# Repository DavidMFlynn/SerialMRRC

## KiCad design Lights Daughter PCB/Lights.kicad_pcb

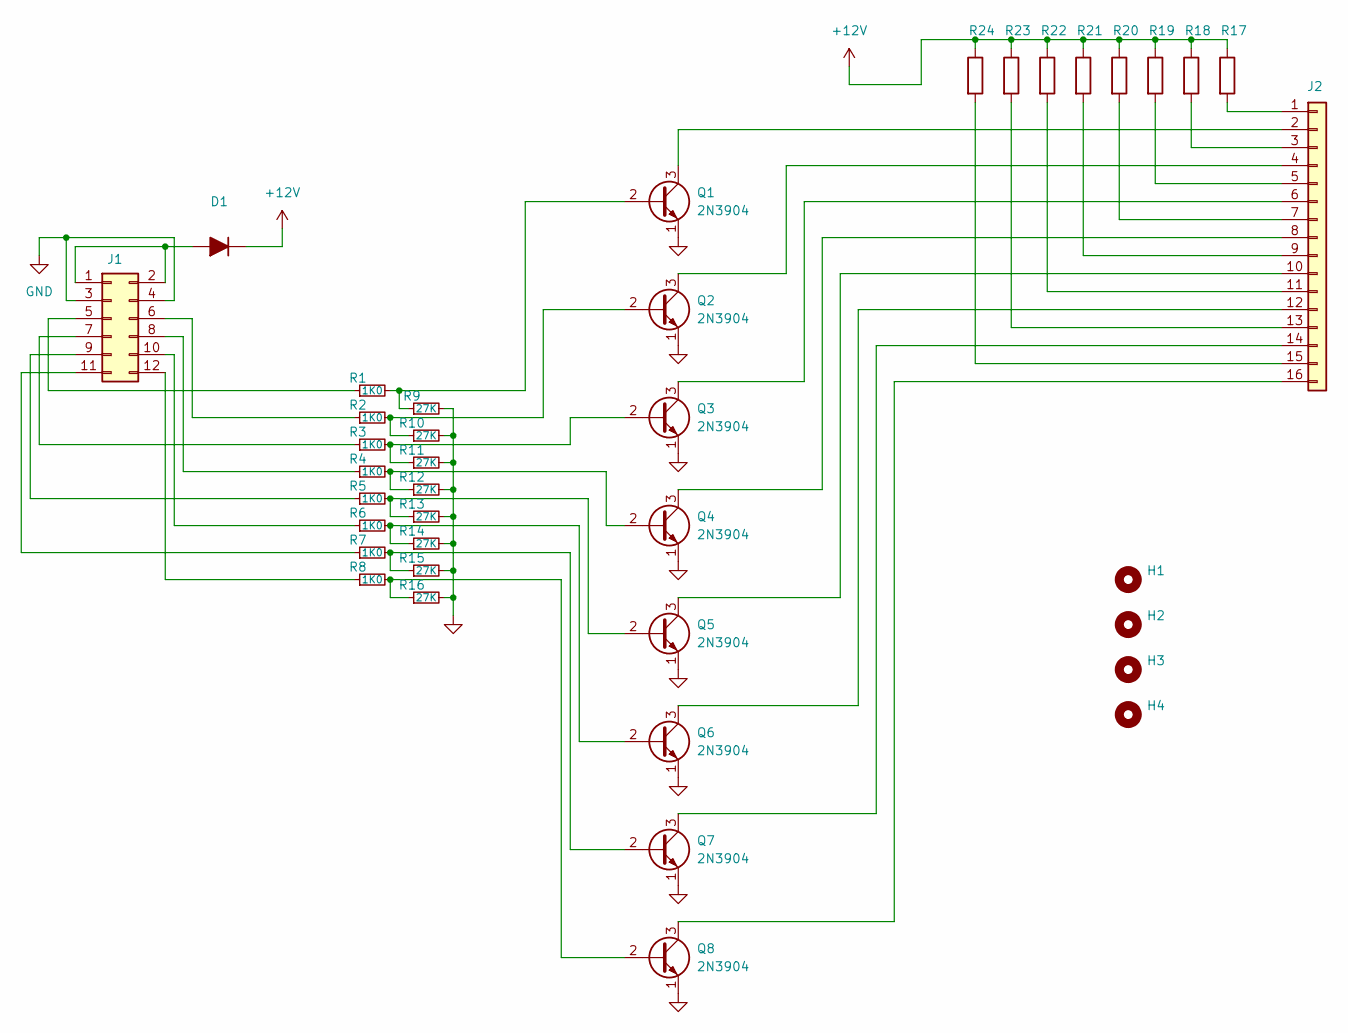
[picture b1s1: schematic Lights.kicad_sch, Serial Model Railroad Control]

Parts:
D1: SMA; D_SMA_Handsoldering
H1, H2, H3, H4: MountingHole; MountingHole_3.2mm_M3
J1: Conn_02x06_Odd_Even; PinHeader_2x06_P2.54mm_Vertical
J2: Conn_01x16; TerminalBlock_Phoenix_PT-1,5-16-3.5-H_1x16_P3.50mm_Horizont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
Q1, Q2, Q3, Q4, Q5, Q6, Q7, Q8: 2N3904; TO-92_Inline
R1, R2, R3, R4, R5, R6, R7, R8: 1K0; R_0805_2012Metric_Pad1.20x1.40mm_HandSolder
R9, R10, R11, R12, R13, R14, R15, R16: 27K; R_0805_2012Metric_Pad1.20x1.40mm_HandSolder
R17, R18, R19, R20, R21, R22, R23, R24: 1K0; R_Axial_DIN0207_L6.3mm_D2.5mm_P10.16mm_Horizontal

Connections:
+12V: D1.1 (K), R17.1, R18.1, R19.1, R20.1, R21.1, R22.1, R23.1, R24.1
GND: J1.3, J1.4, Q1.1 (E), Q2.1 (E), Q3.1 (E), Q4.1 (E), Q5.1 (E), Q6.1 (E), Q7.1 (E), Q8.1 (E), R9.2, R10.2, R11.2, R12.2, R13.2, R14.2, R15.2, R16.2
unnamed: D1.2 (A), J1.1, J1.2
unnamed: J1.5, R1.1
unnamed: J1.6, R2.1
unnamed: J1.7, R3.1
unnamed: J1.8, R4.1
unnamed: J1.9, R5.1
unnamed: J1.10, R6.1
unnamed: J1.11, R7.1
unnamed: J1.12, R8.1
unnamed: J2.1, R17.2
unnamed: J2.2, Q1.3 (C)
unnamed: J2.3, R18.2
unnamed: J2.4, Q2.3 (C)
unnamed: J2.5, R19.2
unnamed: J2.6, Q3.3 (C)
unnamed: J2.7, R20.2
unnamed: J2.8, Q4.3 (C)
unnamed: J2.9, R21.2
unnamed: J2.10, Q5.3 (C)
unnamed: J2.11, R22.2
unnamed: J2.12, Q6.3 (C)
unnamed: J2.13, R23.2
unnamed: J2.14, Q7.3 (C)
unnamed: J2.15, R24.2
unnamed: J2.16, Q8.3 (C)
unnamed: Q1.2 (B), R1.2, R9.1
unnamed: Q2.2 (B), R2.2, R10.1
unnamed: Q3.2 (B), R3.2, R11.1
unnamed: Q4.2 (B), R4.2, R12.1
unnamed: Q5.2 (B), R5.2, R13.1
unnamed: Q6.2 (B), R6.2, R14.1
unnamed: Q7.2 (B), R7.2, R15.1
unnamed: Q8.2 (B), R8.2, R16.1

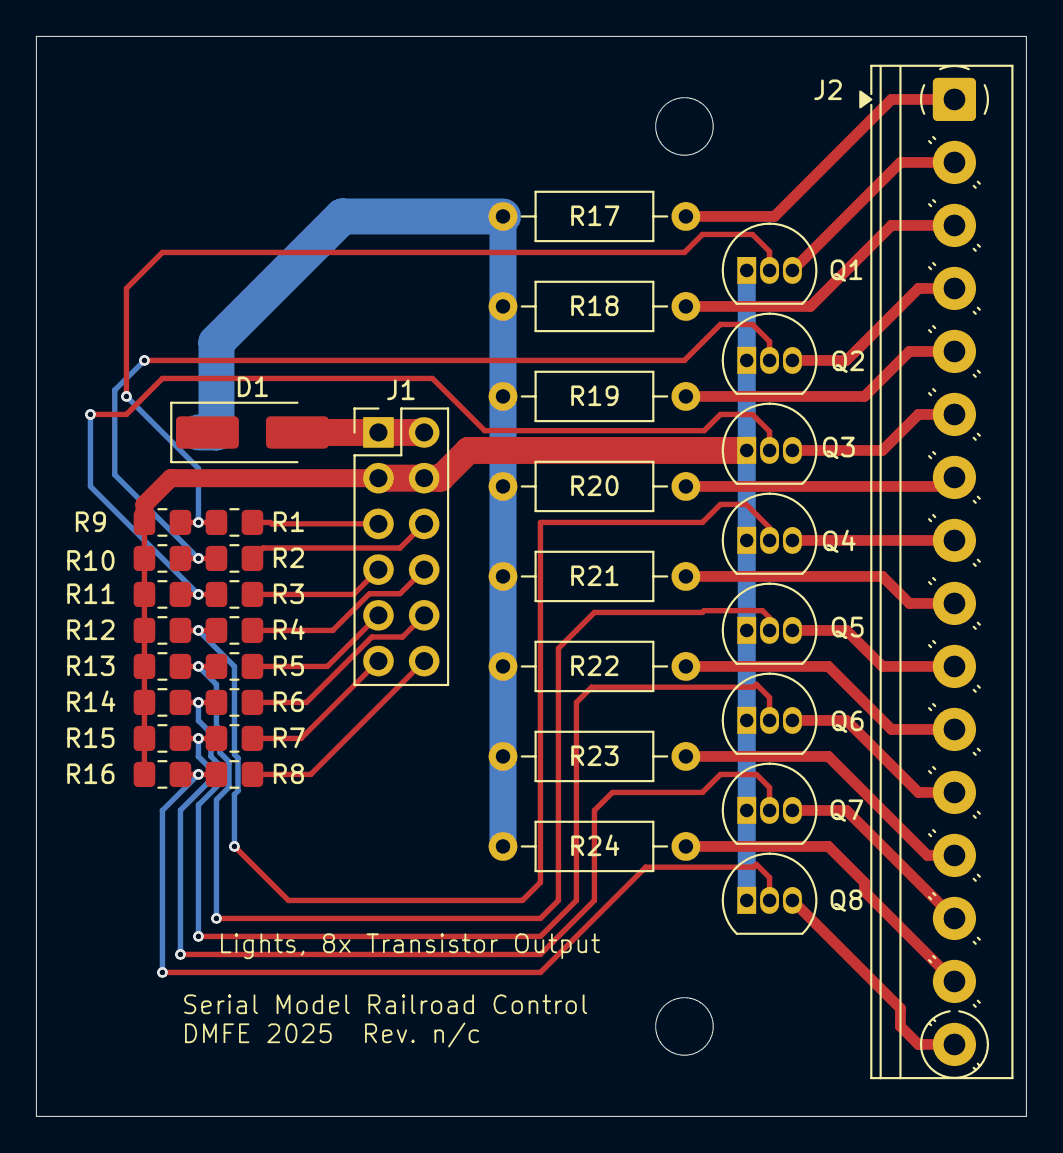
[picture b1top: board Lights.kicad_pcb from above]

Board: 2 copper layers, 55.0 x 60.0 mm, 37 parts (0 on the bottom side), 35 nets.

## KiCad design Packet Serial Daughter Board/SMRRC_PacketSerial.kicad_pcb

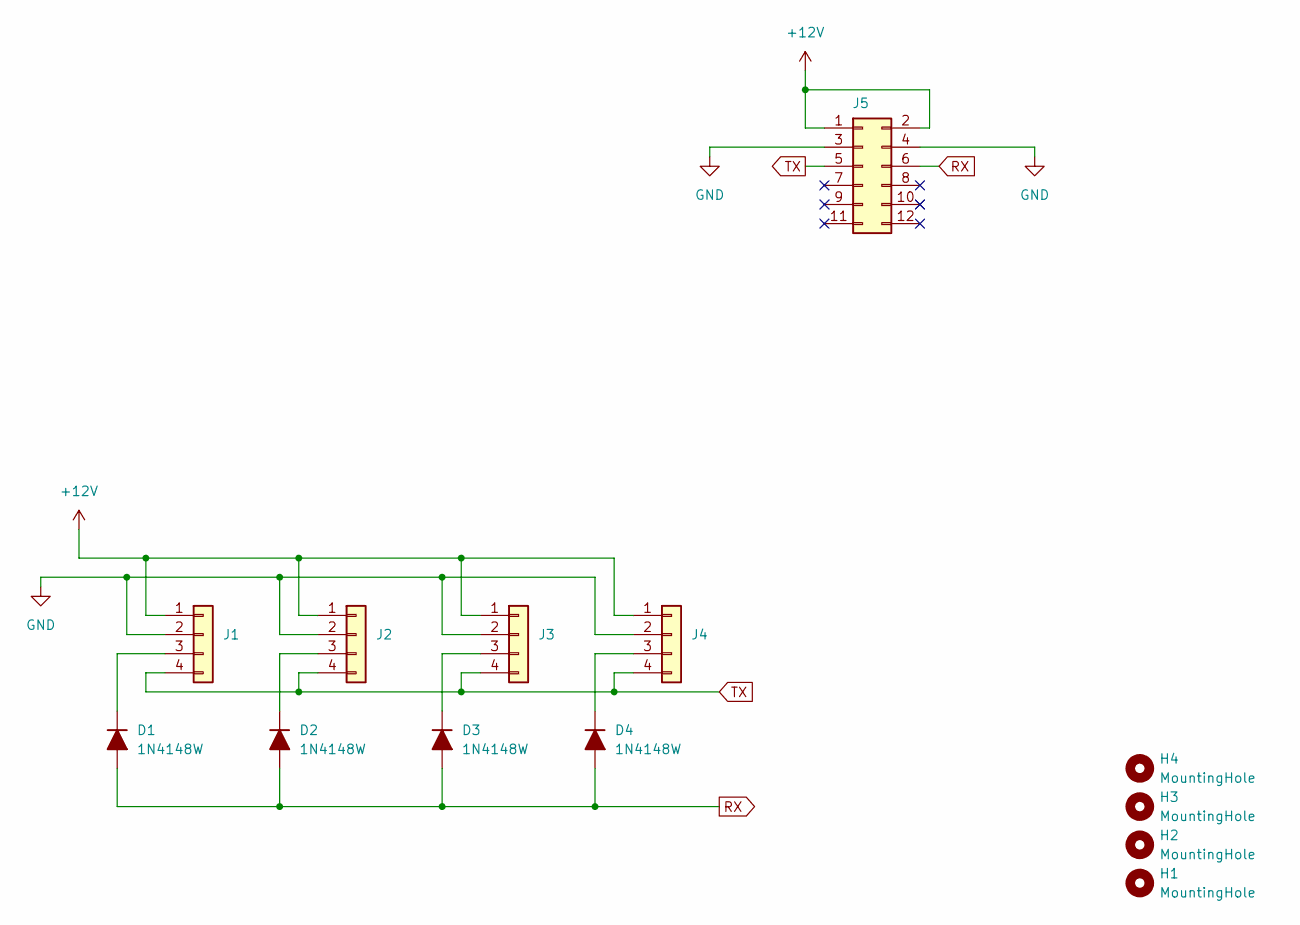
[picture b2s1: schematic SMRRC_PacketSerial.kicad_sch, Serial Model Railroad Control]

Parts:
D1, D2, D3, D4: 1N4148W; D_SOD-123
H1, H2, H3, H4: MountingHole; MountingHole_3.2mm_M3
J1, J2, J3, J4: Conn_01x04; PinHeader_1x04_P2.54mm_Horizontal
J5: Conn_02x06_Odd_Even; PinHeader_2x06_P2.54mm_Vertical

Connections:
+12V: J1.1, J2.1, J3.1, J4.1, J5.1, J5.2
GND: J1.2, J2.2, J3.2, J4.2, J5.3, J5.4
unnamed: D1.1 (K), J1.3
unnamed: D2.1 (K), J2.3
unnamed: D3.1 (K), J3.3
unnamed: D4.1 (K), J4.3
RX: D1.2 (A), D2.2 (A), D3.2 (A), D4.2 (A), J5.6
TX: J1.4, J2.4, J3.4, J4.4, J5.5

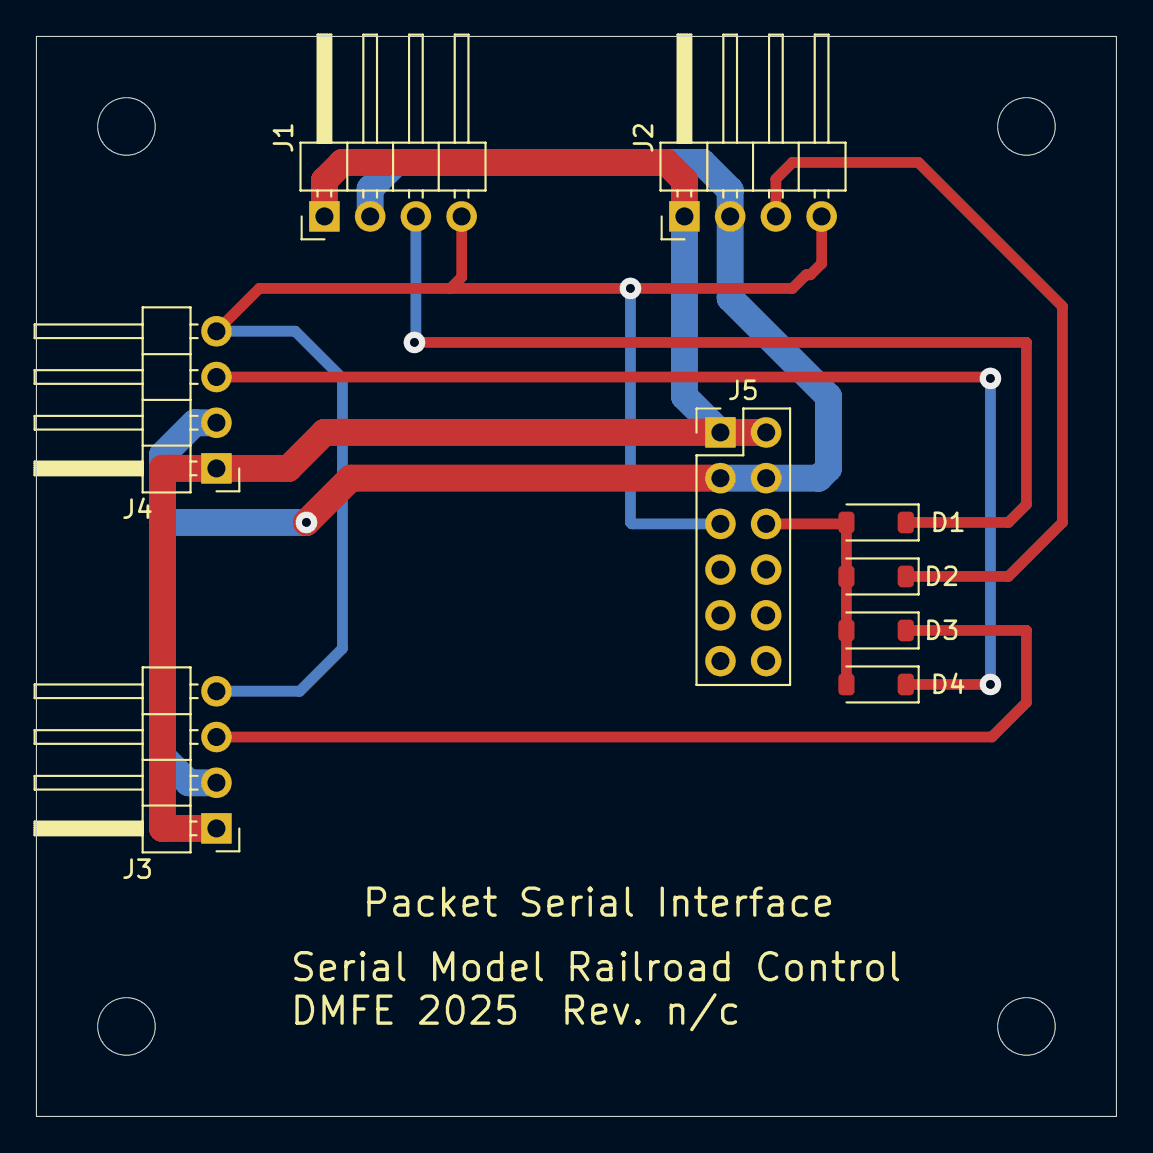
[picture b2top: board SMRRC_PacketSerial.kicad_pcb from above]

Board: 2 copper layers, 60.0 x 60.0 mm, 13 parts (0 on the bottom side), 8 nets.

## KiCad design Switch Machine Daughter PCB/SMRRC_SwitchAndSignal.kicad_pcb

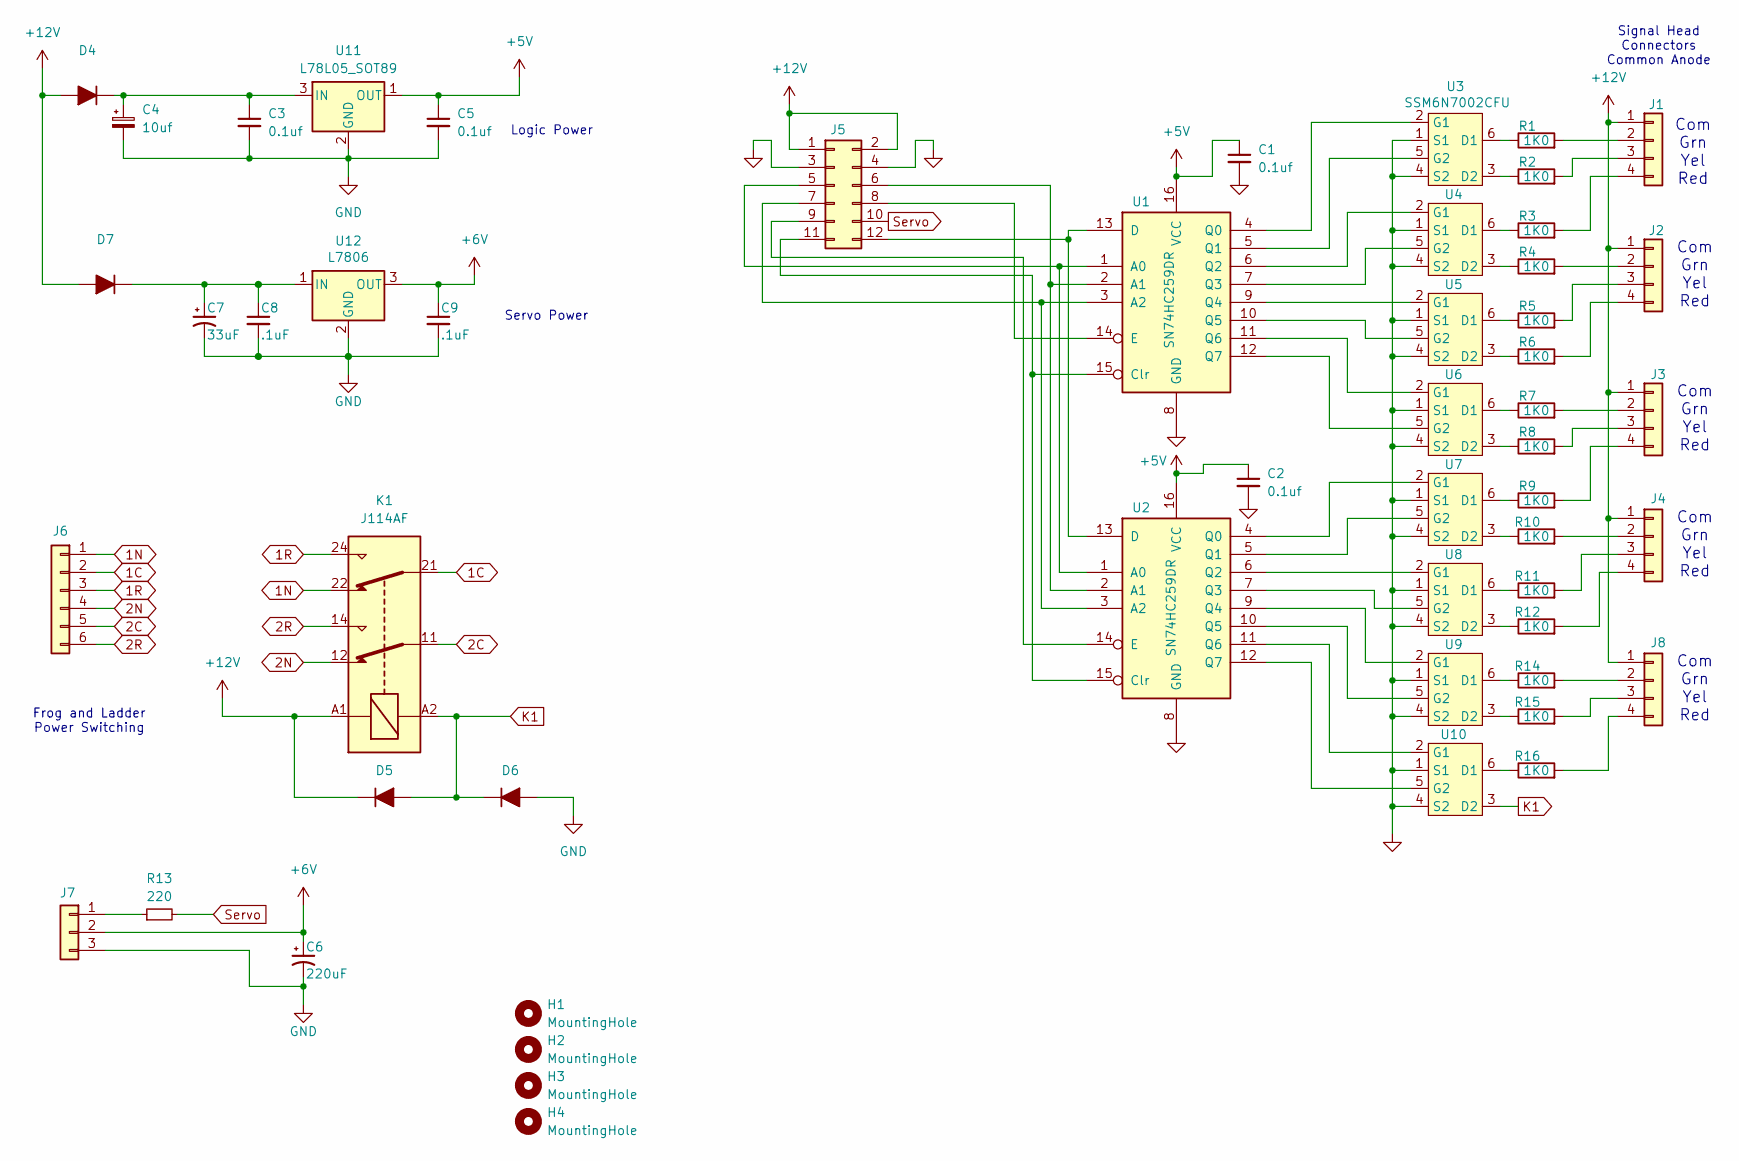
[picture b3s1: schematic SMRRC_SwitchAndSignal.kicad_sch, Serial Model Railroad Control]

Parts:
C1, C2, C3, C5: 0.1uf; C_0805_2012Metric_Pad1.18x1.45mm_HandSolder
C4: 10uf; CP_Radial_D4.0mm_P2.00mm
C6: 220uF; CP_Radial_D6.3mm_P2.50mm
C7: 33uF; CP_Radial_D5.0mm_P2.00mm
C8, C9: .1uF; C_0805_2012Metric_Pad1.18x1.45mm_HandSolder
D4, D5, D6, D7: SMA; D_SMA_Handsoldering
H1, H2, H3, H4: MountingHole; MountingHole_3.2mm_M3
J1, J2, J3, J4, J8: Conn_01x04; TerminalBlock_Phoenix_PT-1,5-4-3.5-H_1x04_P3.50mm_Horizontal
J5: Conn_02x06_Odd_Even; PinHeader_2x06_P2.54mm_Vertical
J6: Conn_01x06; TerminalBlock_MetzConnect_Type059_RT06306HBWC_1x06_P3.50mm_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
J7: Conn_01x03; PinHeader_1x03_P2.54mm_Vertical
K1: J114AF; Relay_DPDT_Finder_40.52
R1, R2, R3, R4, R5, R6, R7, R8, R9, R10, R11, R12, R14, R15, R16: 1K0; R_Axial_DIN0204_L3.6mm_D1.6mm_P7.62mm_Horizontal
R13: 220; R_0805_2012Metric_Pad1.20x1.40mm_HandSolder
U1, U2: SN74HC259DR; SOIC-16W_5.3x10.2mm_P1.27mm
U3, U4, U5, U6, U7, U8, U9, U10: SSM6N7002CFU; SOT-363_SC-70-6_Handsoldering
U11: L78L05_SOT89; SOT-89-3
U12: L7806; TO-263-2

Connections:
1C: J6.2, K1.21
1N: J6.1, K1.22
1R: J6.3, K1.24
2C: J6.5, K1.11
2N: J6.4, K1.12
2R: J6.6, K1.14
+5V: C1.1, C2.1, C5.1, U1.16 (VCC), U2.16 (VCC), U11.1 (OUT)
+6V: C6.1, C9.1, J7.2, U12.3 (OUT)
+12V: D4.2 (A), D5.1 (K), D7.2 (A), J1.1, J2.1, J3.1, J4.1, J5.1, J5.2, J8.1, K1.A1
GND: C1.2, C2.2, C3.2, C4.2, C5.2, C6.2, C7.2, C8.2, C9.2, D6.2 (A), J5.3, J5.4, J7.3, U1.8 (GND), U2.8 (GND), U3.1 (S1), U3.4 (S2), U4.1 (S1), U4.4 (S2), U5.1 (S1), U5.4 (S2), U6.1 (S1), U6.4 (S2), U7.1 (S1), U7.4 (S2), U8.1 (S1), U8.4 (S2), U9.1 (S1), U9.4 (S2), U10.1 (S1), U10.4 (S2), U11.2 (GND), U12.2 (GND)
K1: D5.2 (A), D6.1 (K), K1.A2, U10.3 (D2)
unnamed: C3.1, C4.1, D4.1 (K), U11.3 (IN)
unnamed: C7.1, C8.1, D7.1 (K), U12.1 (IN)
unnamed: J1.2, R1.2
unnamed: J1.3, R2.2
unnamed: J1.4, R3.2
unnamed: J2.2, R4.2
unnamed: J2.3, R5.2
unnamed: J2.4, R6.2
unnamed: J3.2, R7.2
unnamed: J3.3, R8.2
unnamed: J3.4, R9.2
unnamed: J4.2, R10.2
unnamed: J4.3, R11.2
unnamed: J4.4, R12.2
unnamed: J5.5, U1.1 (A0), U2.1 (A0)
unnamed: J5.6, U1.2 (A1), U2.2 (A1)
unnamed: J5.7, U1.3 (A2), U2.3 (A2)
unnamed: J5.8, U1.14 (E)
unnamed: J5.9, U2.14 (E)
unnamed: J5.11, U1.15 (Clr), U2.15 (Clr)
unnamed: J5.12, U1.13 (D), U2.13 (D)
unnamed: J7.1, R13.1
unnamed: J8.2, R14.2
unnamed: J8.3, R15.2
unnamed: J8.4, R16.2
unnamed: U1.4 (Q0), U3.2 (G1)
unnamed: U1.5 (Q1), U3.5 (G2)
unnamed: U1.6 (Q2), U4.2 (G1)
unnamed: U1.7 (Q3), U4.5 (G2)
unnamed: U1.9 (Q4), U5.2 (G1)
unnamed: U1.10 (Q5), U5.5 (G2)
unnamed: U1.11 (Q6), U6.2 (G1)
unnamed: U1.12 (Q7), U6.5 (G2)
unnamed: U2.4 (Q0), U7.2 (G1)
unnamed: U2.5 (Q1), U7.5 (G2)
unnamed: U2.6 (Q2), U8.2 (G1)
unnamed: U2.7 (Q3), U8.5 (G2)
unnamed: U2.9 (Q4), U9.2 (G1)
unnamed: U2.10 (Q5), U9.5 (G2)
unnamed: R1.1, U3.6 (D1)
unnamed: R2.1, U3.3 (D2)
unnamed: R3.1, U4.6 (D1)
unnamed: R4.1, U4.3 (D2)
unnamed: R5.1, U5.6 (D1)
unnamed: R6.1, U5.3 (D2)
unnamed: R7.1, U6.6 (D1)
unnamed: R8.1, U6.3 (D2)
unnamed: R9.1, U7.6 (D1)
unnamed: R10.1, U7.3 (D2)
unnamed: R11.1, U8.6 (D1)
unnamed: R12.1, U8.3 (D2)
unnamed: R14.1, U9.6 (D1)
unnamed: R15.1, U9.3 (D2)
unnamed: R16.1, U10.6 (D1)
unnamed: U2.11 (Q6), U10.2 (G1)
unnamed: U2.12 (Q7), U10.5 (G2)
Servo: J5.10, R13.2

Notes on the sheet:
Servo Power
Com Grn Yel Red
Frog and Ladder Power Switching
Logic Power
Signal Head Connectors Common Anode

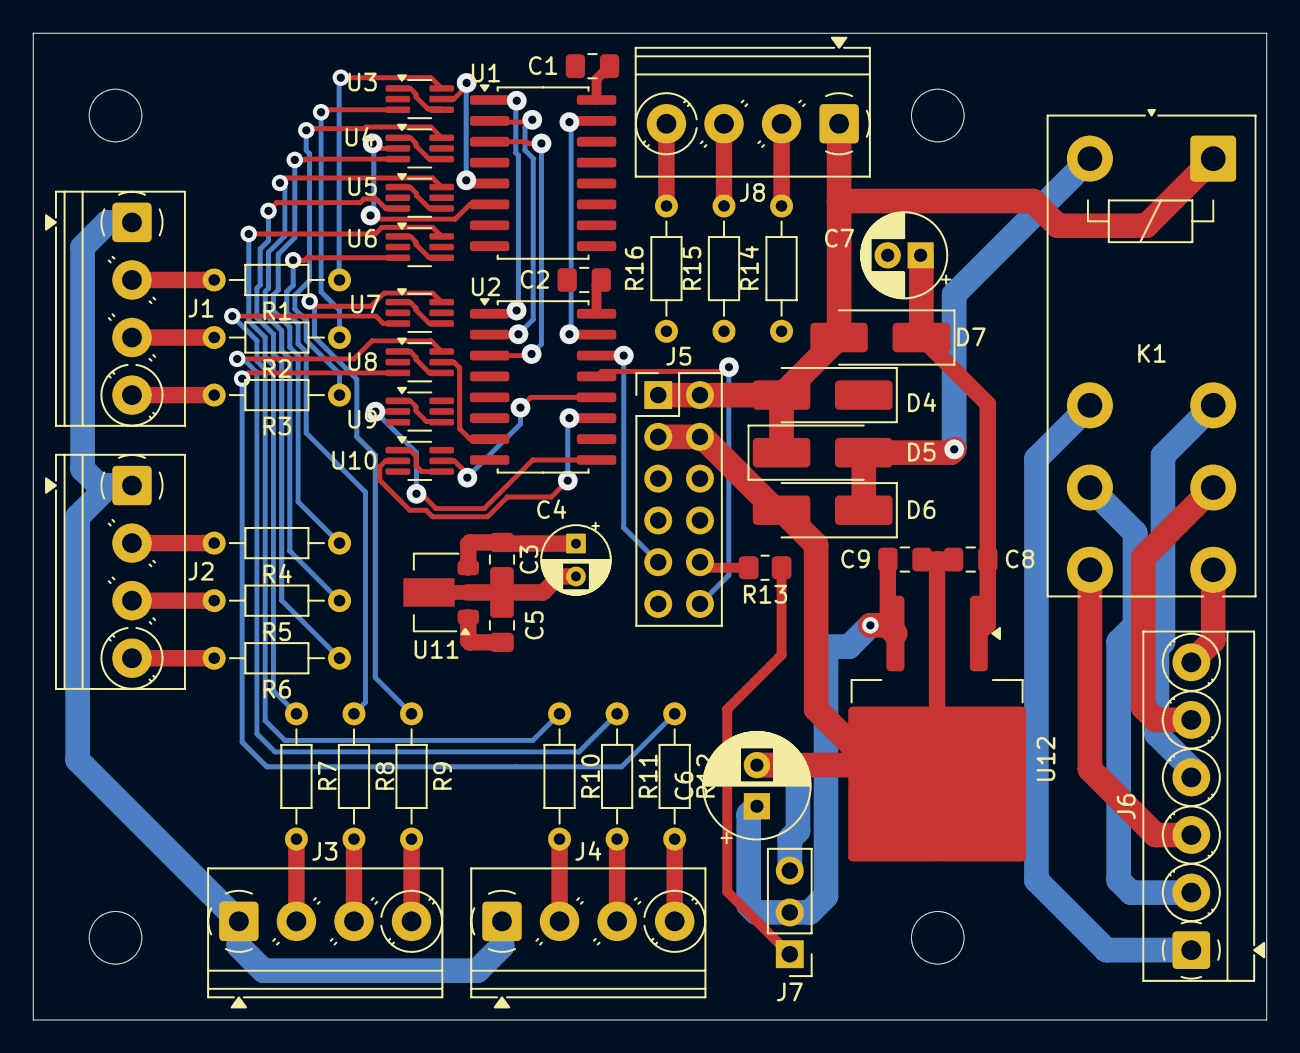
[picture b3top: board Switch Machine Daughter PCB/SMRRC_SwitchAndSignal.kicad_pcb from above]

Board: 2 copper layers, 75.0 x 60.0 mm, 54 parts (0 on the bottom side), 68 nets.

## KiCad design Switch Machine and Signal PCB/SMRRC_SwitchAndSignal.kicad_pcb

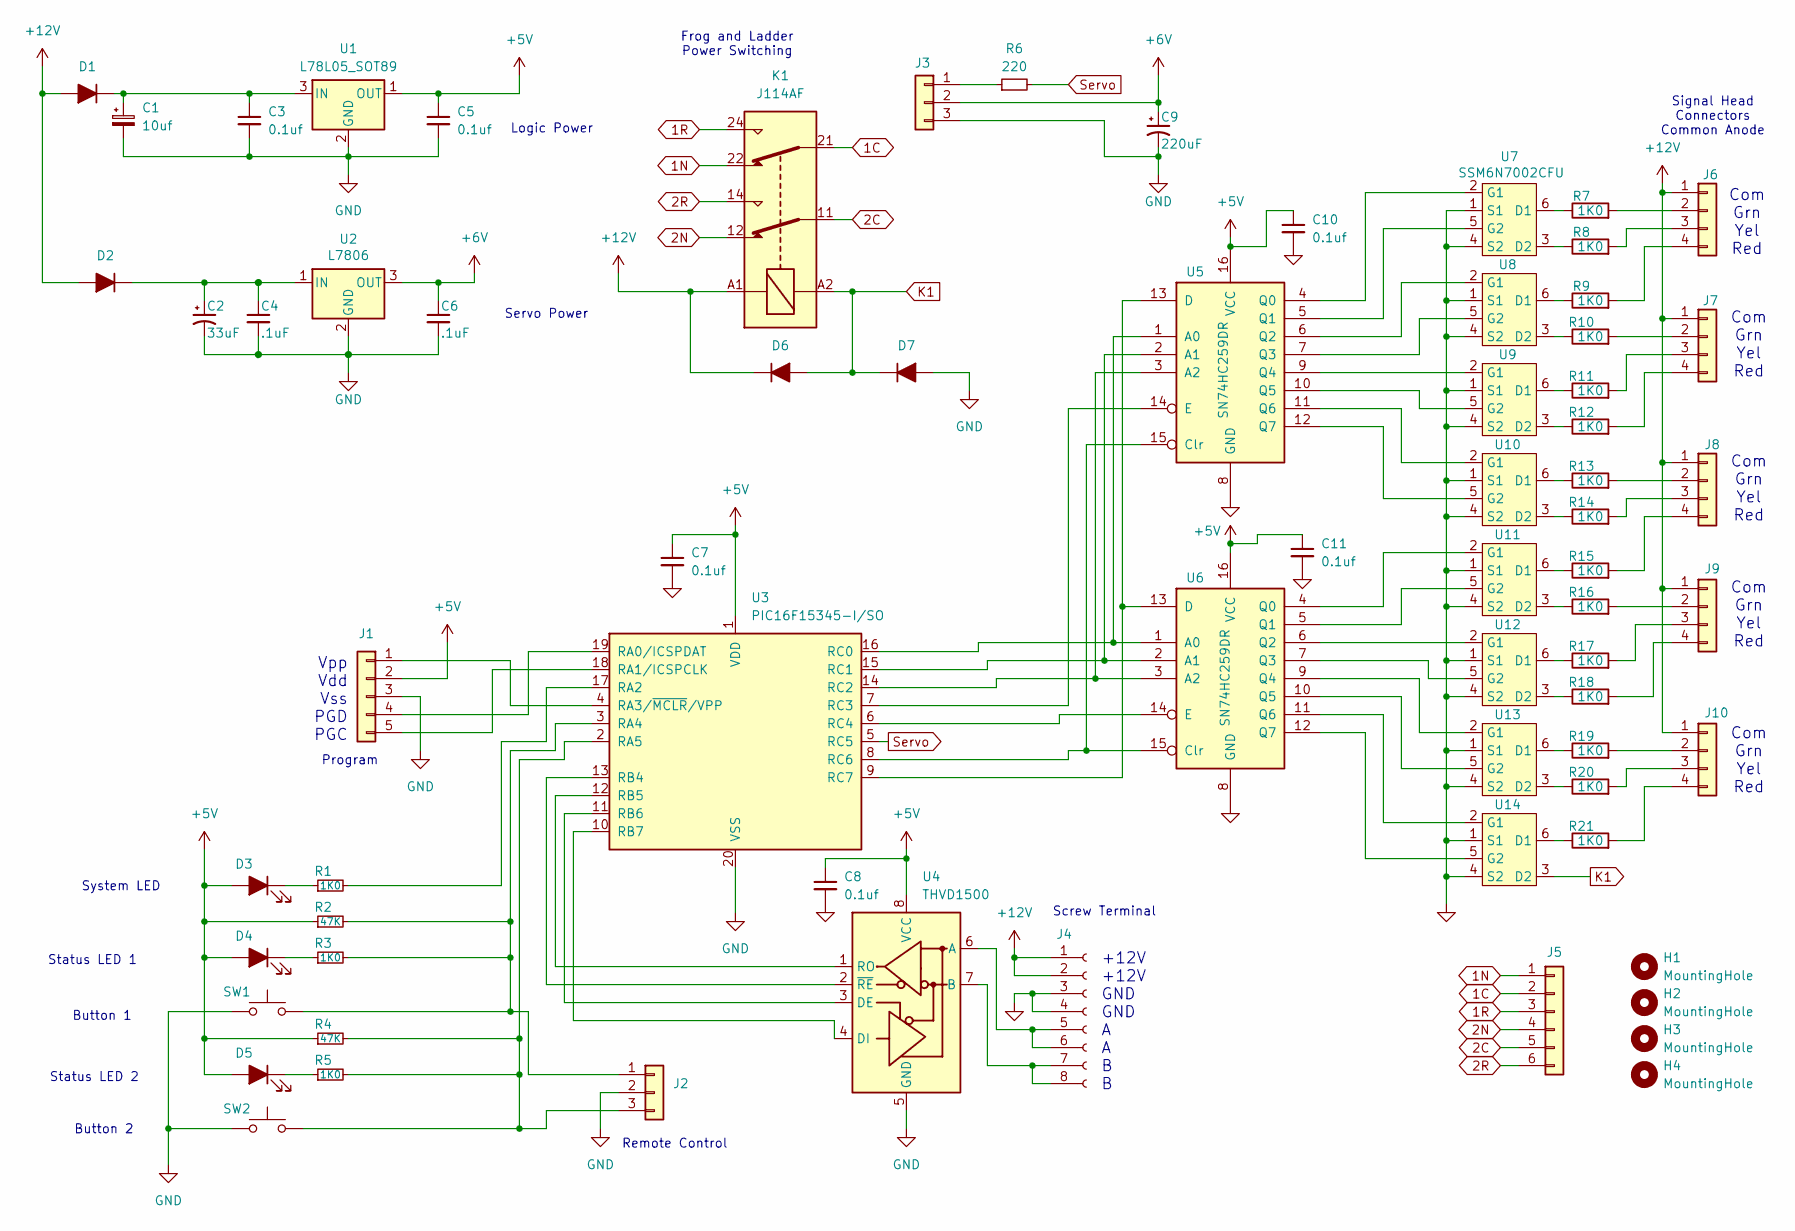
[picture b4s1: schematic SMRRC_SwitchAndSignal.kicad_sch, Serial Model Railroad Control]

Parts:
C1: 10uf; CP_Radial_D4.0mm_P2.00mm
C2: 33uF; CP_Radial_D5.0mm_P2.00mm
C3, C5, C7, C8, C10, C11: 0.1uf; C_0805_2012Metric_Pad1.18x1.45mm_HandSolder
C4, C6: .1uF; C_0805_2012Metric_Pad1.18x1.45mm_HandSolder
C9: 220uF; CP_Radial_D6.3mm_P2.50mm
D1, D2, D6, D7: SMA; D_SMA_Handsoldering
D3, D4, D5: LED_Filled; D_1206_3216Metric_Pad1.42x1.75mm_HandSolder
H1, H2, H3, H4: MountingHole; MountingHole_3.2mm_M3
J1: Conn_01x05; PinHeader_1x05_P2.54mm_Vertical
J2: Conn_01x03; PinSocket_1x03_P2.54mm_Vertical
J3: Conn_01x03; PinHeader_1x03_P2.54mm_Vertical
J4: Conn_01x08_Socket; TerminalBlock_MaiXu_MX126-5.0-08P_1x08_P5.00mm
J5: Conn_01x06; TerminalBlock_MetzConnect_Type059_RT06306HBWC_1x06_P3.50mm_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
J6, J7, J8, J9, J10: Conn_01x04; TerminalBlock_Phoenix_PT-1,5-4-3.5-H_1x04_P3.50mm_Horizontal
K1: J114AF; Relay_DPDT_Finder_40.52
R1, R3, R5: 1K0; R_0805_2012Metric_Pad1.20x1.40mm_HandSolder
R2, R4: 47K; R_0805_2012Metric_Pad1.20x1.40mm_HandSolder
R6: 220; R_0805_2012Metric_Pad1.20x1.40mm_HandSolder
R7, R8, R9, R10, R11, R12, R13, R14, R15, R16, R17, R18, R19, R20, R21: 1K0; R_Axial_DIN0204_L3.6mm_D1.6mm_P7.62mm_Horizontal
SW1, SW2: SW_Push; SW_SPST_PTS645
U1: L78L05_SOT89; SOT-89-3
U2: L7806; TO-263-2
U3: PIC16F15345-I/SO; SOIC-20W_7.5x12.8mm_P1.27mm
U4: THVD1500; SOIC-8_3.9x4.9mm_P1.27mm
U5, U6: SN74HC259DR; SOIC-16W_5.3x10.2mm_P1.27mm
U7, U8, U9, U10, U11, U12, U13, U14: SSM6N7002CFU; SOT-363_SC-70-6_Handsoldering

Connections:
1C: J5.2, K1.21
1N: J5.1, K1.22
1R: J5.3, K1.24
2C: J5.5, K1.11
2N: J5.4, K1.12
2R: J5.6, K1.14
+5V: C5.1, C7.1, C8.1, C10.1, C11.1, D3.2 (A), D4.2 (A), D5.2 (A), J1.2, R2.1, R4.1, U1.1 (OUT), U3.1 (VDD), U4.8 (VCC), U5.16 (VCC), U6.16 (VCC)
+6V: C6.1, C9.1, J3.2, U2.3 (OUT)
+12V: D1.2 (A), D2.2 (A), D6.1 (K), J4.1, J4.2, J6.1, J7.1, J8.1, J9.1, J10.1, K1.A1
GND: C1.2, C2.2, C3.2, C4.2, C5.2, C6.2, C7.2, C8.2, C9.2, C10.2, C11.2, D7.2 (A), J1.3, J2.2, J3.3, J4.3, J4.4, SW1.1, SW2.1, U1.2 (GND), U2.2 (GND), U3.20 (VSS), U4.5 (GND), U5.8 (GND), U6.8 (GND), U7.1 (S1), U7.4 (S2), U8.1 (S1), U8.4 (S2), U9.1 (S1), U9.4 (S2), U10.1 (S1), U10.4 (S2), U11.1 (S1), U11.4 (S2), U12.1 (S1), U12.4 (S2), U13.1 (S1), U13.4 (S2), U14.1 (S1), U14.4 (S2)
K1: D6.2 (A), D7.1 (K), K1.A2, U14.3 (D2)
unnamed: C1.1, C3.1, D1.1 (K), U1.3 (IN)
unnamed: C2.1, C4.1, D2.1 (K), U2.1 (IN)
unnamed: D3.1 (K), R1.1
unnamed: D4.1 (K), R3.1
unnamed: D5.1 (K), R5.1
unnamed: J1.1, U3.4 (RA3/~MCLR/VPP)
unnamed: J1.4, U3.19 (RA0/ICSPDAT)
unnamed: J1.5, U3.18 (RA1/ICSPCLK)
unnamed: J2.1, R2.2, R3.2, SW1.2, U3.3 (RA4)
unnamed: J2.3, R4.2, R5.2, SW2.2, U3.2 (RA5)
unnamed: J3.1, R6.1
unnamed: J4.5, J4.6, U4.6 (A)
unnamed: J4.7, J4.8, U4.7 (B)
unnamed: J6.2, R7.2
unnamed: J6.3, R8.2
unnamed: J6.4, R9.2
unnamed: J7.2, R10.2
unnamed: J7.3, R11.2
unnamed: J7.4, R12.2
unnamed: J8.2, R13.2
unnamed: J8.3, R14.2
unnamed: J8.4, R15.2
unnamed: J9.2, R16.2
unnamed: J9.3, R17.2
unnamed: J9.4, R18.2
unnamed: J10.2, R19.2
unnamed: J10.3, R20.2
unnamed: J10.4, R21.2
unnamed: R1.2, U3.17 (RA2)
unnamed: U3.13 (RB4), U4.2 (~RE)
unnamed: U3.12 (RB5), U4.1 (RO)
unnamed: U3.11 (RB6), U4.3 (DE)
unnamed: U3.10 (RB7), U4.4 (DI)
unnamed: U3.16 (RC0), U5.1 (A0), U6.1 (A0)
unnamed: U3.15 (RC1), U5.2 (A1), U6.2 (A1)
unnamed: U3.14 (RC2), U5.3 (A2), U6.3 (A2)
unnamed: U3.7 (RC3), U5.14 (E)
unnamed: U3.6 (RC4), U6.14 (E)
unnamed: U3.8 (RC6), U5.15 (Clr), U6.15 (Clr)
unnamed: U3.9 (RC7), U5.13 (D), U6.13 (D)
unnamed: U5.4 (Q0), U7.2 (G1)
unnamed: U5.5 (Q1), U7.5 (G2)
unnamed: U5.6 (Q2), U8.2 (G1)
unnamed: U5.7 (Q3), U8.5 (G2)
unnamed: U5.9 (Q4), U9.2 (G1)
unnamed: U5.10 (Q5), U9.5 (G2)
unnamed: R7.1, U7.6 (D1)
unnamed: R8.1, U7.3 (D2)
unnamed: R9.1, U8.6 (D1)
unnamed: R10.1, U8.3 (D2)
unnamed: R11.1, U9.6 (D1)
unnamed: R12.1, U9.3 (D2)
unnamed: R13.1, U10.6 (D1)
unnamed: R14.1, U10.3 (D2)
unnamed: U5.11 (Q6), U10.2 (G1)
unnamed: U5.12 (Q7), U10.5 (G2)
unnamed: R15.1, U11.6 (D1)
unnamed: R16.1, U11.3 (D2)
unnamed: U6.4 (Q0), U11.2 (G1)
unnamed: U6.5 (Q1), U11.5 (G2)
unnamed: R17.1, U12.6 (D1)
unnamed: R18.1, U12.3 (D2)
unnamed: U6.6 (Q2), U12.2 (G1)
unnamed: U6.7 (Q3), U12.5 (G2)
unnamed: R19.1, U13.6 (D1)
unnamed: R20.1, U13.3 (D2)
unnamed: U6.9 (Q4), U13.2 (G1)
unnamed: U6.10 (Q5), U13.5 (G2)
unnamed: R21.1, U14.6 (D1)
unnamed: U6.11 (Q6), U14.2 (G1)
unnamed: U6.12 (Q7), U14.5 (G2)
Servo: R6.2, U3.5 (RC5)

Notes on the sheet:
Servo Power
Remote Control
Vpp Vdd Vss PGD PGC
Com Grn Yel Red
Button 2
Screw Terminal
Program
+12V +12V GND GND A A B B
Status LED 2
Button 1
Frog and Ladder Power Switching
Status LED 1
Logic Power
System LED
Signal Head Connectors Common Anode

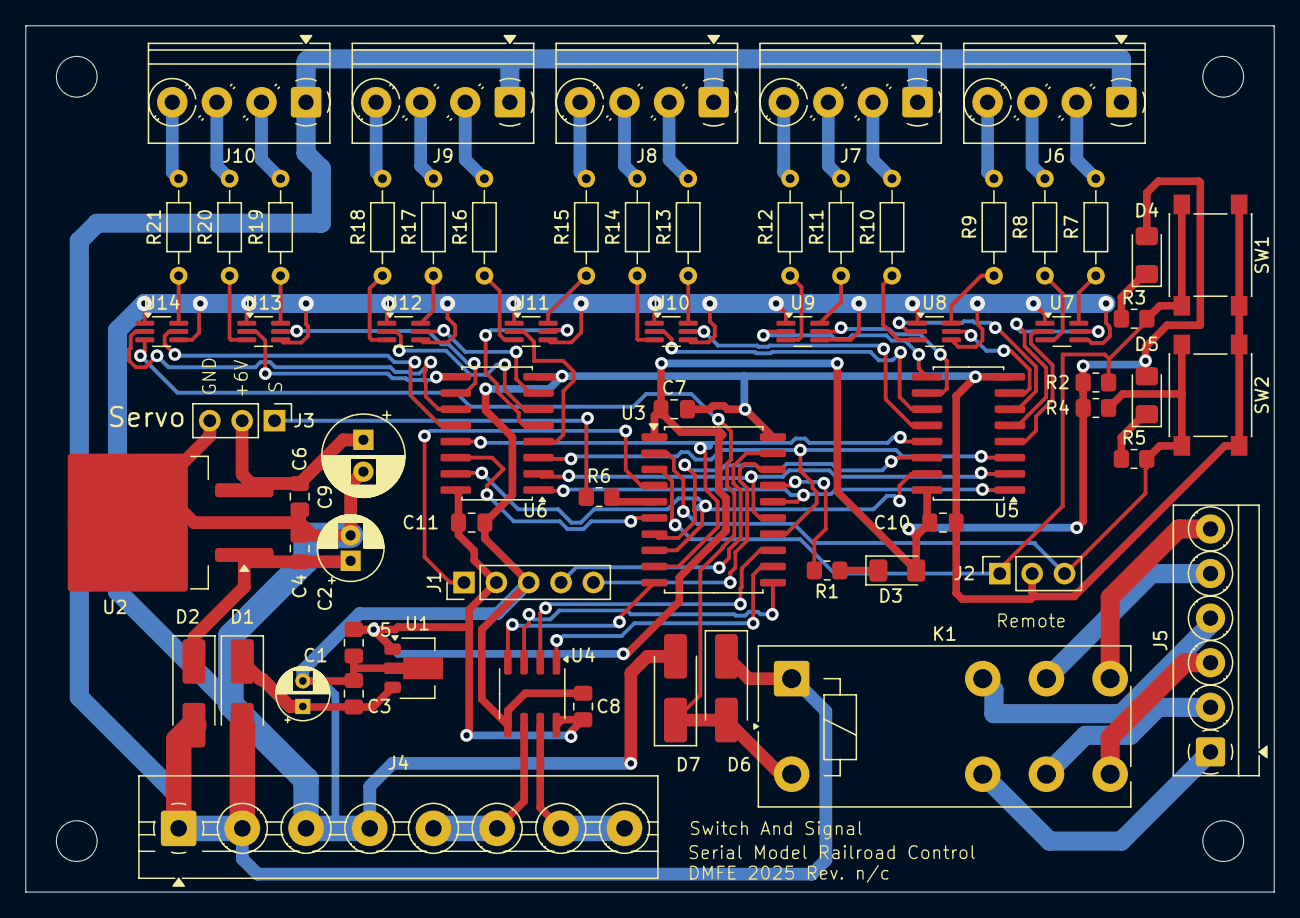
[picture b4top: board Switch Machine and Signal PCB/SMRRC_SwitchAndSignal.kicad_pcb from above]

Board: 2 copper layers, 98.0 x 68.0 mm, 70 parts (0 on the bottom side), 83 nets.
